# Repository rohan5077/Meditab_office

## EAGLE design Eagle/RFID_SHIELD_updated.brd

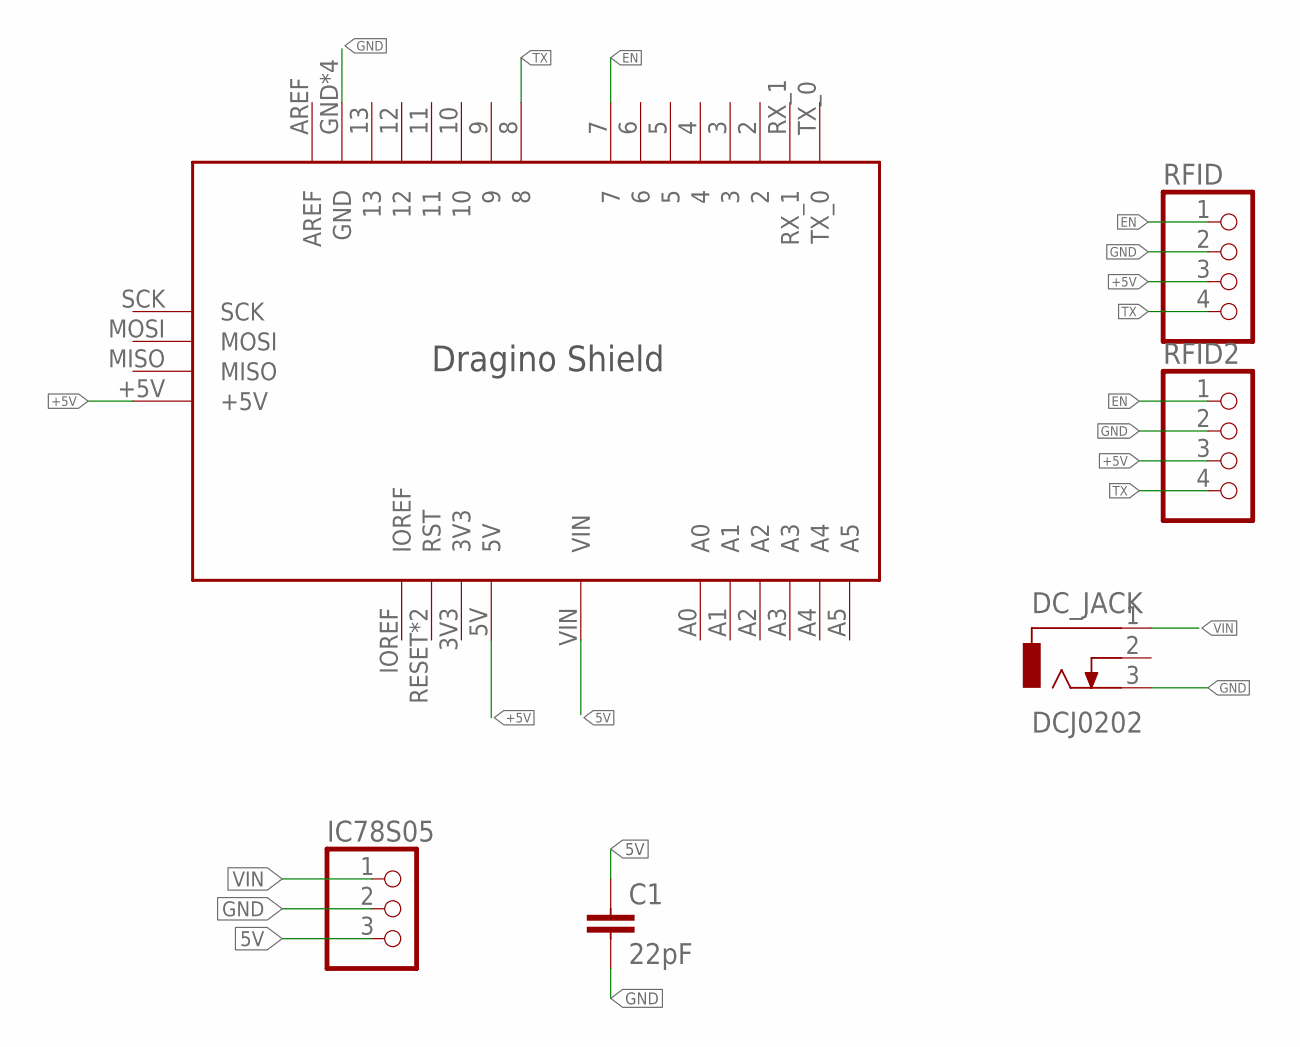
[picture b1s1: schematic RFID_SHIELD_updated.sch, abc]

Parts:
C1: 22pF; C2.5-3
DC_JACK: DCJ0202
IC78S05: PINHD-1X3; 1X03
RFID, RFID2: PINHD-1X4; 1X04
U$1: DRAGINO_SHIELD

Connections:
5V: C1.1, IC78S05.3, U$1.VIN
+5V: RFID.3, RFID2.3, U$1.5V, U$1.+5V
EN: RFID.1, RFID2.1, U$1.7
GND: C1.2, DC_JACK.3, IC78S05.2, RFID.2, RFID2.2, U$1.GND, U$1.GND@1 (GND), U$1.GND@2 (GND), U$1.GND@3 (GND)
TX: RFID.4, RFID2.4, U$1.8
VIN: DC_JACK.1, IC78S05.1

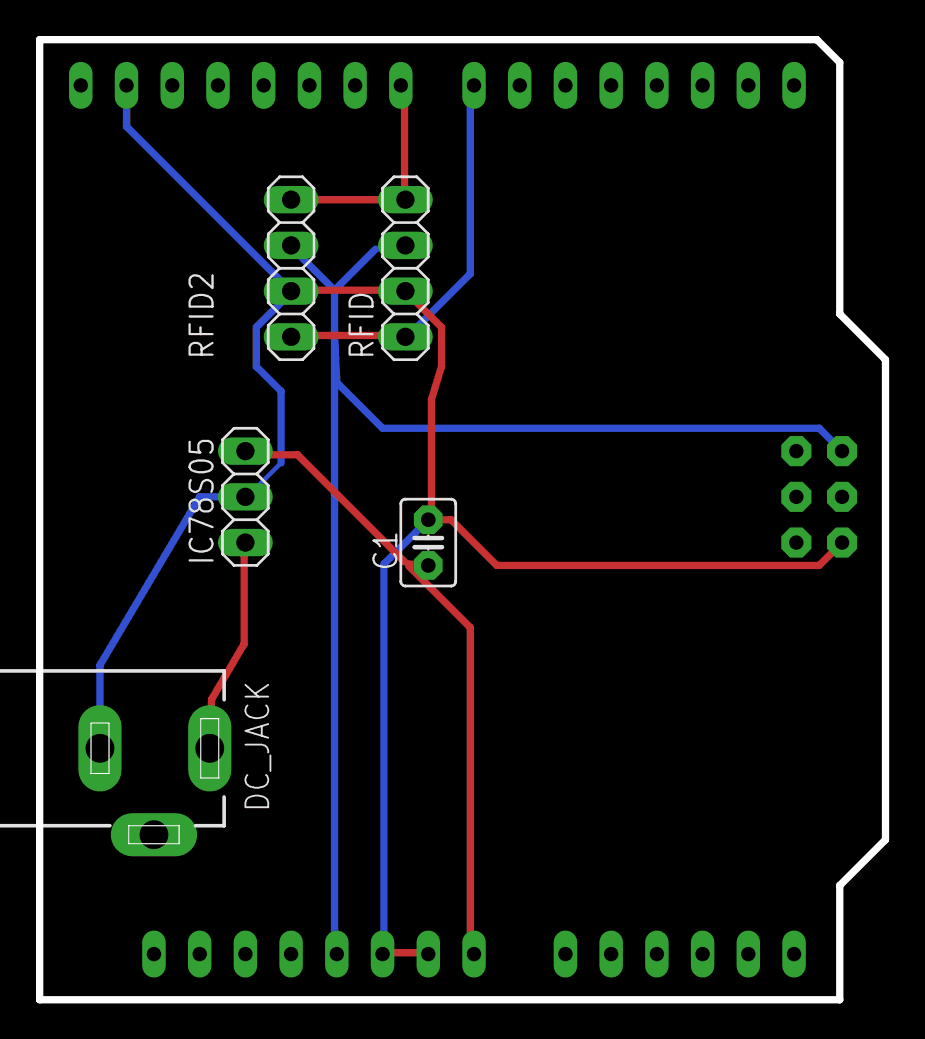
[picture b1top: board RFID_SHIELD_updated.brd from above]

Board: 2 copper layers, 47.0 x 53.3 mm, 6 parts (0 on the bottom side), 6 nets.

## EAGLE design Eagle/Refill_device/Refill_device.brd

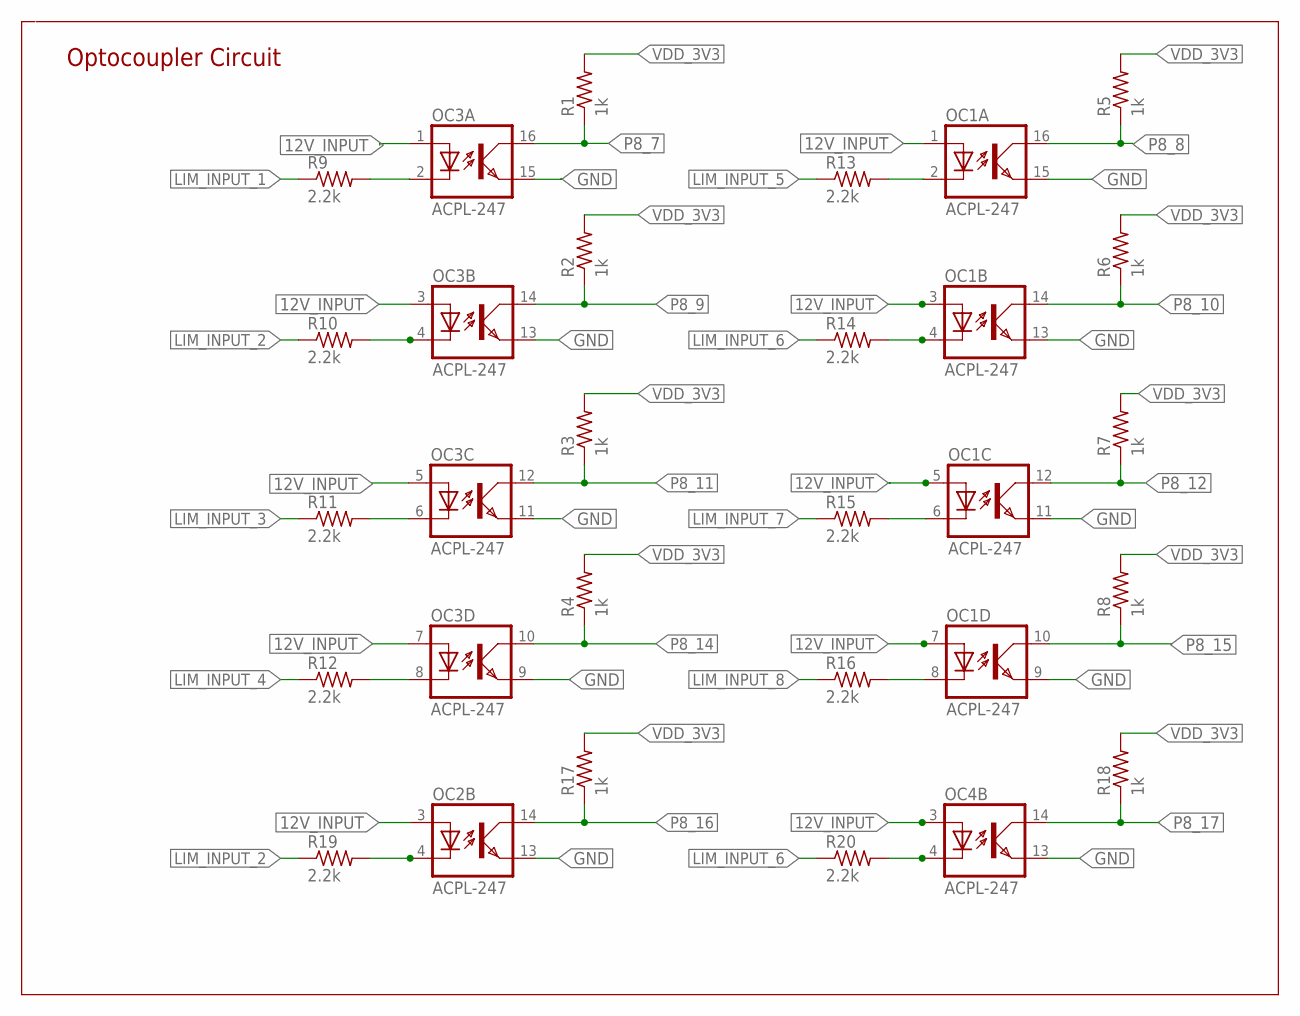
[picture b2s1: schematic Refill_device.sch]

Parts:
OC1, OC2, OC3, OC4: ACPL-247; SOP16
R1, R2, R3, R4, R5, R6, R7, R8, R17, R18: 1k; R0603
R9, R10, R11, R12, R13, R14, R15, R16, R19, R20: 2.2k; R0603

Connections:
12V_INPUT: OC1.1 (A), OC1.3 (A), OC1.5 (A), OC1.7 (A), OC2.3 (A), OC3.1 (A), OC3.3 (A), OC3.5 (A), OC3.7 (A), OC4.3 (A)
GND: OC1.9 (EMIT), OC1.11 (EMIT), OC1.13 (EMIT), OC1.15 (EMIT), OC2.13 (EMIT), OC3.9 (EMIT), OC3.11 (EMIT), OC3.13 (EMIT), OC3.15 (EMIT), OC4.13 (EMIT)
LIM_INPUT_1: R9.1
LIM_INPUT_2: R10.1, R19.1
LIM_INPUT_3: R11.1
LIM_INPUT_4: R12.1
LIM_INPUT_5: R13.1
LIM_INPUT_6: R14.1, R20.1
LIM_INPUT_7: R15.1
LIM_INPUT_8: R16.1
unnamed: OC4.4 (C), R20.2
unnamed: OC2.4 (C), R19.2
unnamed: OC1.2 (C), R13.2
unnamed: OC1.4 (C), R14.2
unnamed: OC1.6 (C), R15.2
unnamed: OC1.8 (C), R16.2
unnamed: OC3.6 (C), R11.2
unnamed: OC3.8 (C), R12.2
unnamed: OC3.2 (C), R9.2
unnamed: OC3.4 (C), R10.2
P8_7: OC3.16 (COL), R1.1
P8_8: OC1.16 (COL), R5.1
P8_9: OC3.14 (COL), R2.1
P8_10: OC1.14 (COL), R6.1
P8_11: OC3.12 (COL), R3.1
P8_12: OC1.12 (COL), R7.1
P8_14: OC3.10 (COL), R4.1
P8_15: OC1.10 (COL), R8.1
P8_16: OC2.14 (COL), R17.1
P8_17: OC4.14 (COL), R18.1
VDD_3V3: R1.2, R2.2, R3.2, R4.2, R5.2, R6.2, R7.2, R8.2, R17.2, R18.2

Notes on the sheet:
Optocoupler Circuit

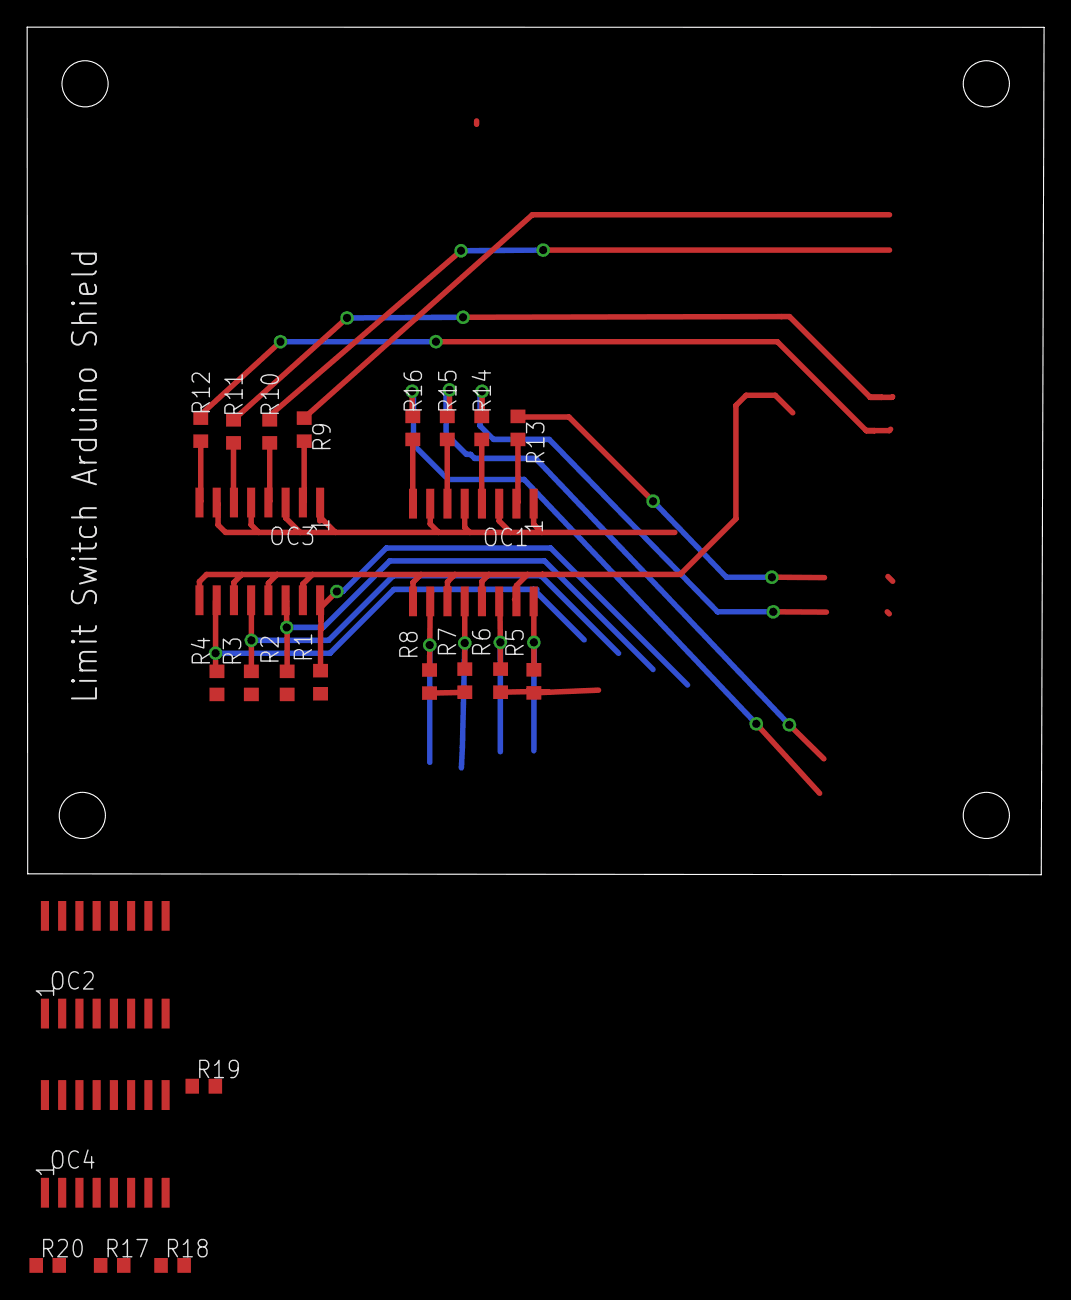
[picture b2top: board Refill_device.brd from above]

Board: 2 copper layers, 74.9 x 62.4 mm, 24 parts (0 on the bottom side), 25 nets.

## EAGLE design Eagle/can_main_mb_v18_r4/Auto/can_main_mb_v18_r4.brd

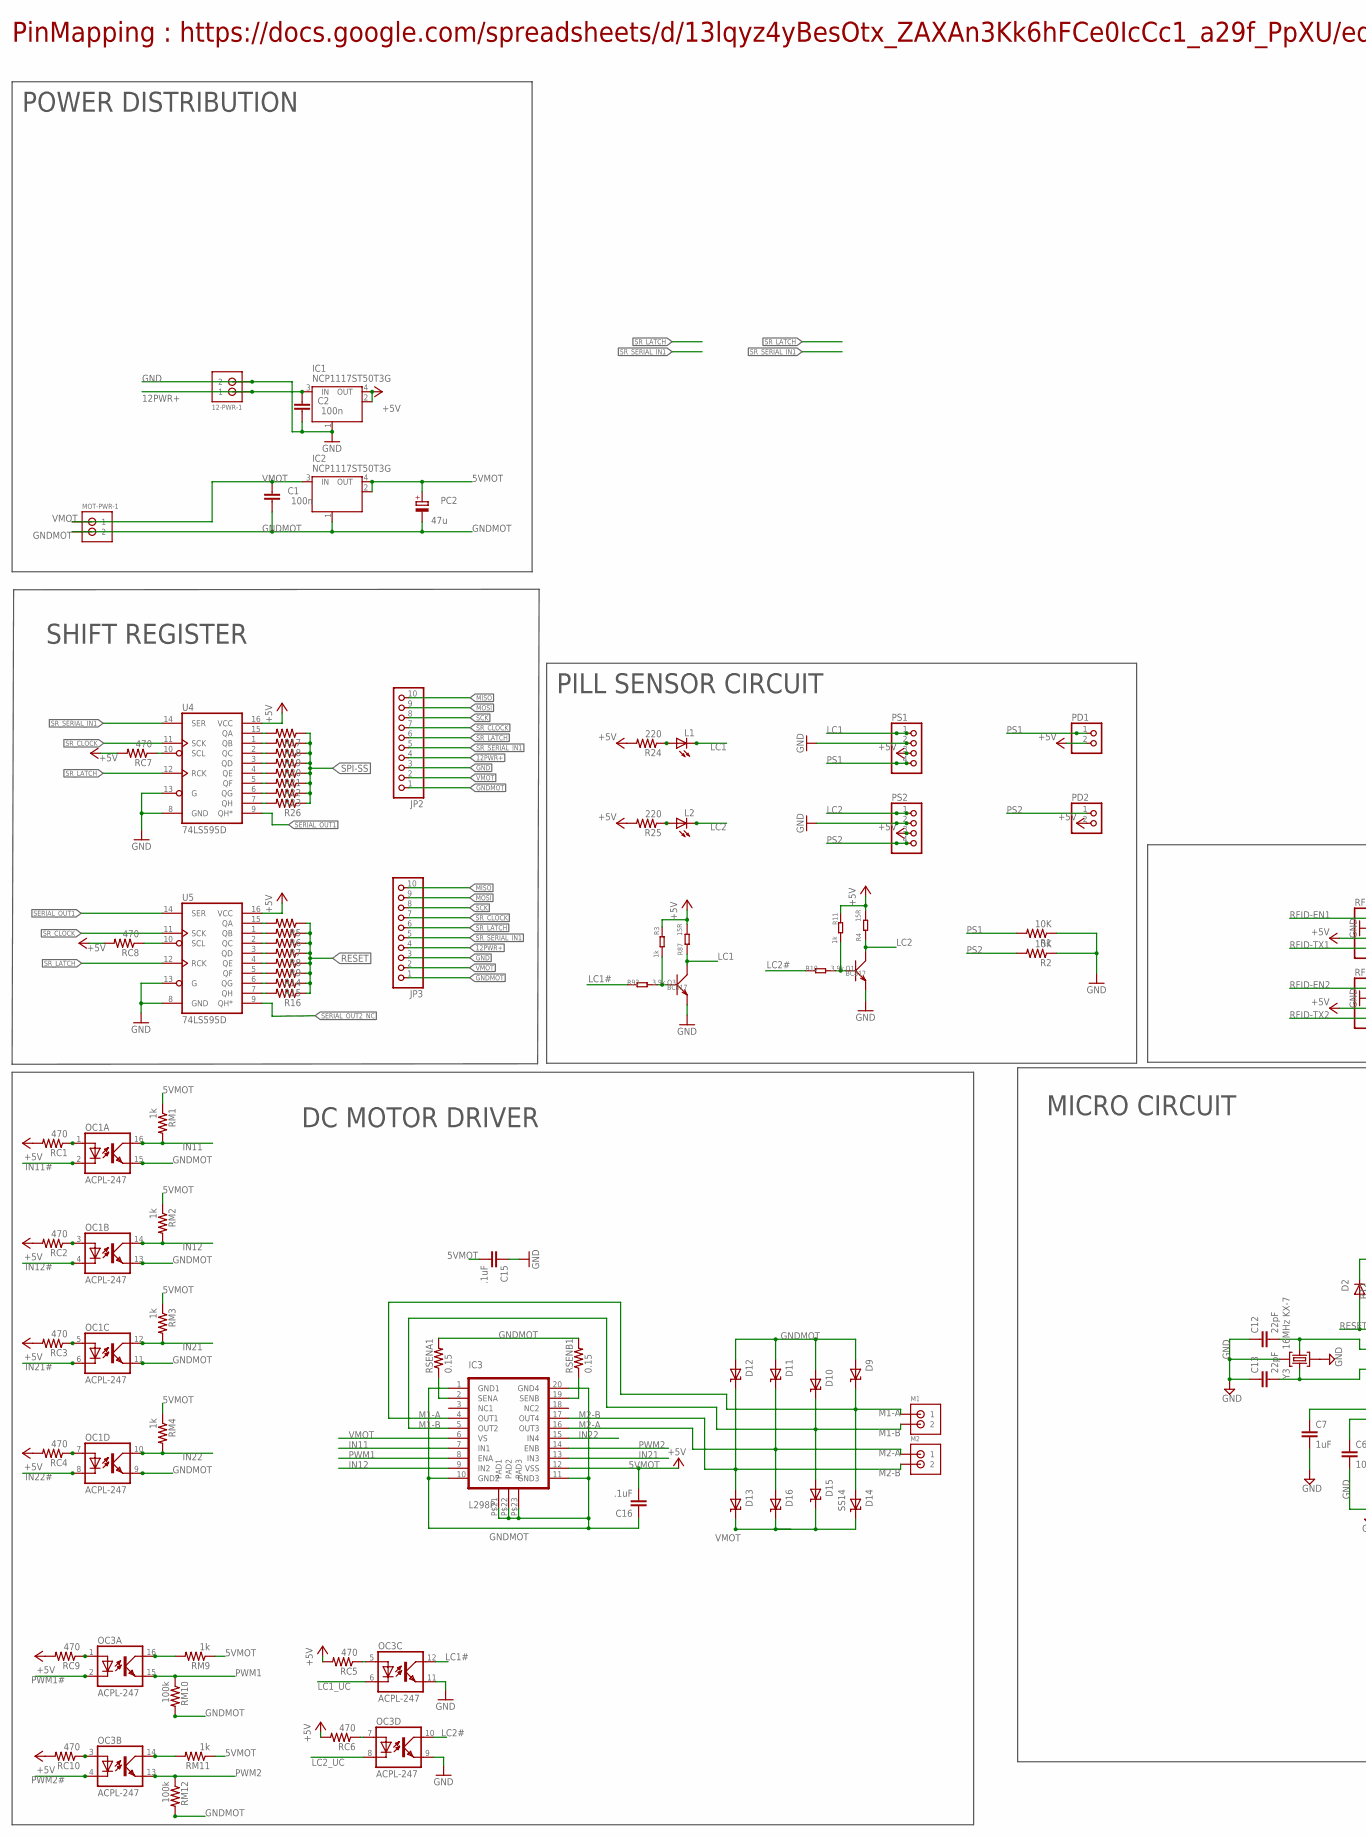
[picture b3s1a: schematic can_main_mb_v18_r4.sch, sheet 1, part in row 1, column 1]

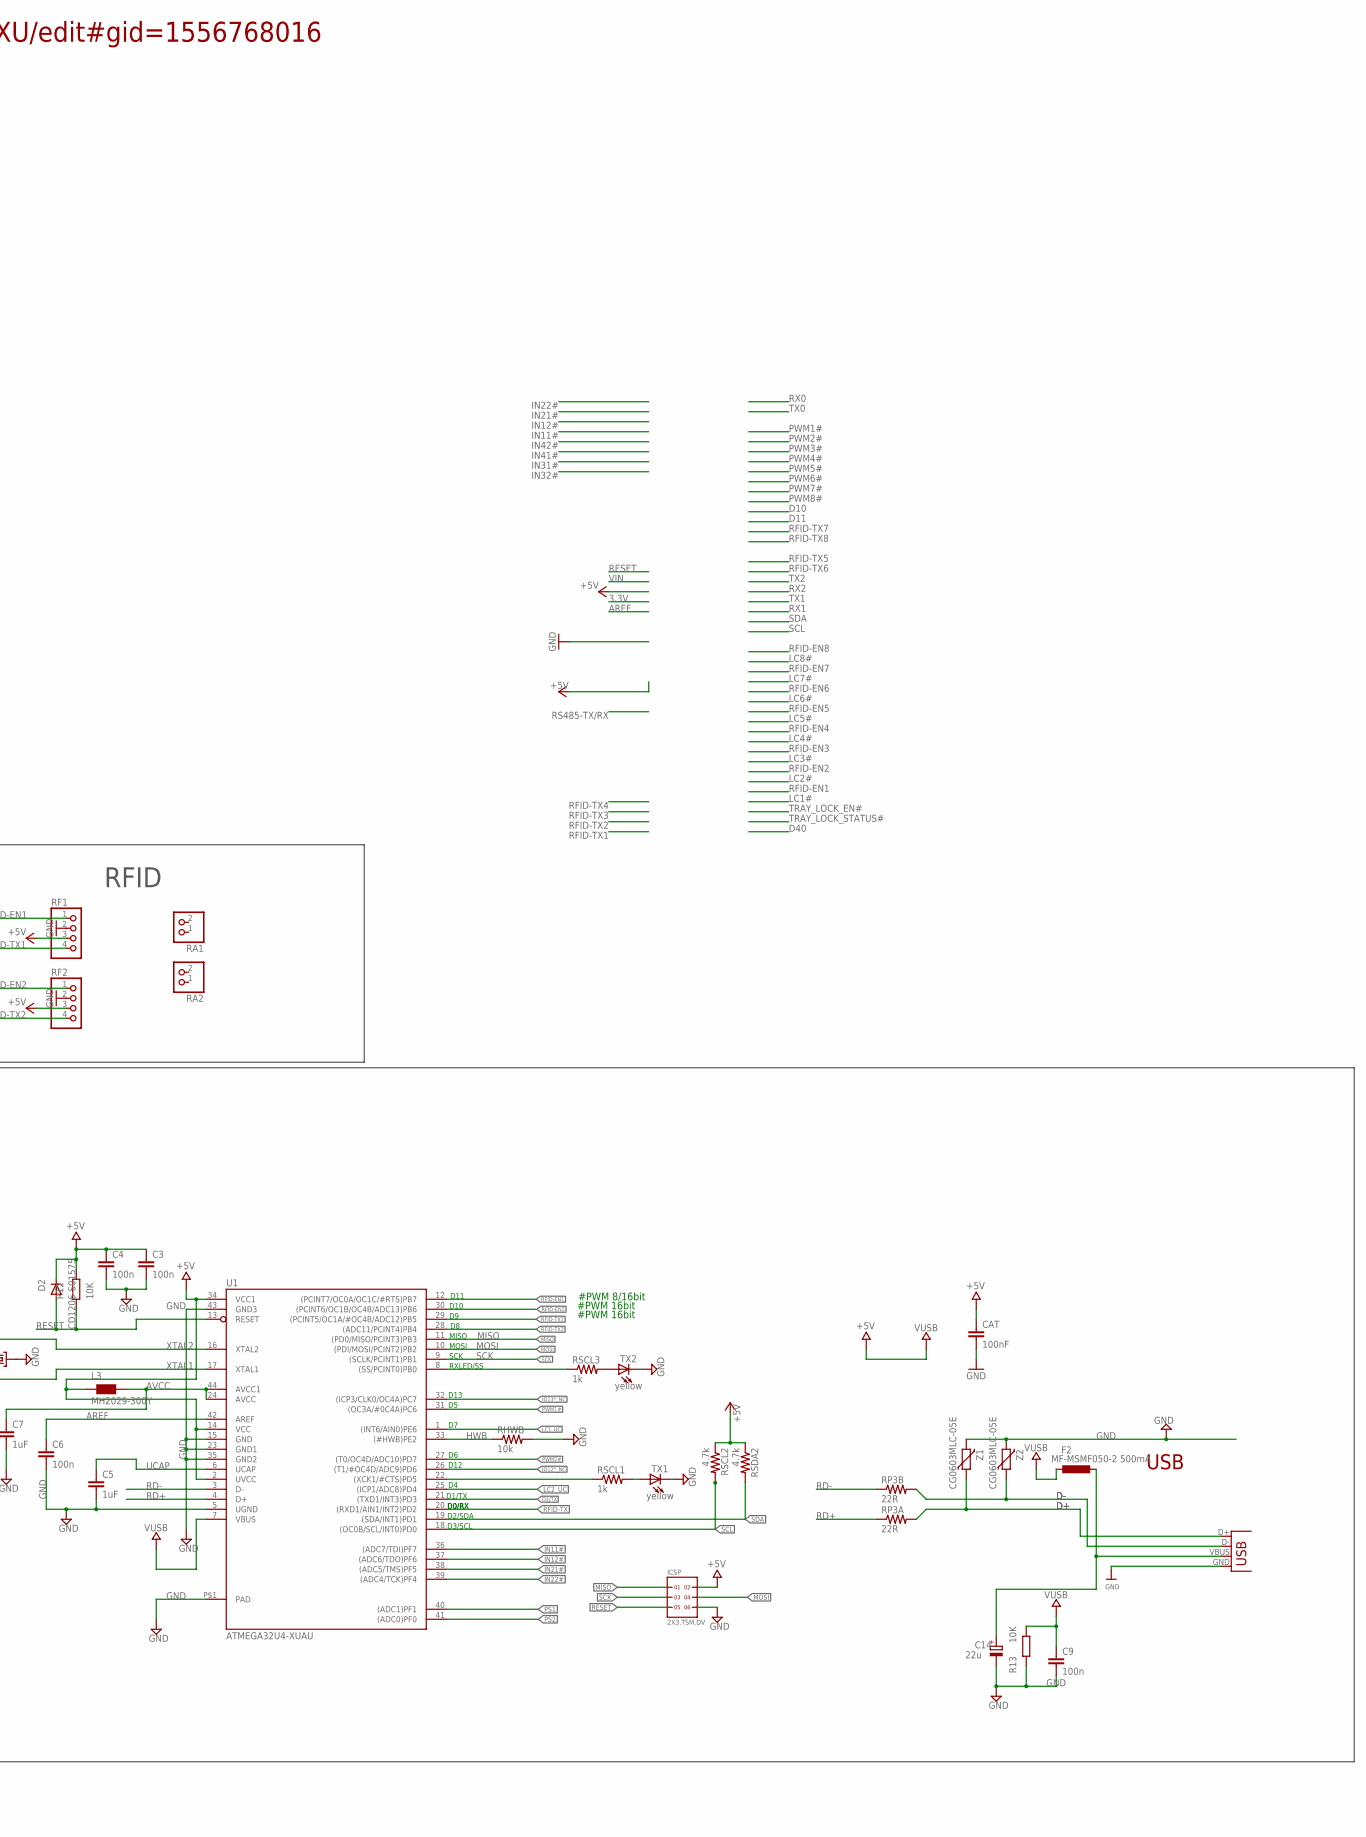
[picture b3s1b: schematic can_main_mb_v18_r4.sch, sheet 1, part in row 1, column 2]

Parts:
12-PWR-1: JST-PH_2-PIN_HEADER; JST_B2B-PH_HEADER
C1, C2: 100n; C0603
C3, C4, C6, C9: 100n; C0603K
C5, C7: 1uF; C0603K
C12, C13: 22pF; C0603K
C14: 22u; SMC_C
C15, C16: .1uF; 0402-CAP
CAT: 100nF; 0603
D2: CD1206-S01575; MINIMELF
D9, D10, D11, D12, D13, D14, D15, D16: SS14; SMA
F2: MF-MSMF050-2 500mA; L1812
IC1, IC2: NCP1117ST50T3G; SOT223
IC3: L298P; POWER-SO20
ICSP: 2X3.TSM.DV; TSM-103-XX-XXX-DV-A
JP1: USB; USB-B-PTH-VERTICAL
JP2, JP3: PINHD-1X10; 1X10
L1, L2: LED5MM
L3: MH2029-300Y; 0805
M1, M2: JST-PH_2-PIN_HEADER; JST_B2B-PH_HEADER
MOT-PWR-1: JST-PH_2-PIN_HEADER; JST_B2B-PH_HEADER
OC1, OC3: ACPL-247; SOP16
PC2: 47u; PANASONIC_D
PD1, PD2: PINHD-1X2; 1X02
PS1, PS2: PINHD-1X4; 1X04
Q1, Q3: BC817; SOT23
R1, R2: 10K; R0603
R3, R11: 1k; R0603
R4, R87: 15R; R0603
R5, R6, R7, R8, R9, R14, R15, R16, R17, R18, R19, R20, R21, R22, R23, R26: R-US_R0603; R0603
R10, R93: 3.9k; R0603
R12, R13: 10K; R0603-ROUND
R24, R25: 220; R0603
RA1, RA2: PINHD-1X2; 1X02
RC1, RC2, RC3, RC4, RC5, RC6, RC7, RC8, RC9, RC10: 470; R0603
RF1, RF2: PINHD-1X4; 1X04
RHWB: 10k; R0603
RM1, RM2, RM3, RM4, RM9, RM11: 1k; R0603
RM10, RM12: 100k; R0603
RP3A, RP3B: 22R; R0603
RSCL1, RSCL3: 1k; R0603
RSCL2: 4.7k; R0603
RSDA2: 4.7k; R0603
RSENA1: 0.15; R0603
RSENB1: 0.15; R0603
TX1, TX2: yellow; CHIPLED_0603
U1: ATMEGA32U4-XUAU; TQFP44-PAD
U4, U5: 74LS595D; SO16
Y3: 16MHz KX-7; CRYSTAL-3.2-2.5
Z1, Z2: CG0603MLC-05E; CT/CN0603

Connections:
5VMOT: C15.2, C16.2, IC2.2 (OUT), IC2.4 (OUT), IC3.P$12 (VSS), PC2.+, RM1.1, RM2.1, RM3.1, RM4.1, RM9.1, RM11.1
12PWR+: 12-PWR-1.P1 (1), C2.2, IC1.3 (IN), JP2.4, JP3.4
+5V: C3.1, C4.1, C9.1, CAT.1, D2.C, F2.2, IC1.2 (OUT), IC1.4 (OUT), ICSP.2, L3.1, PD1.2, PD2.2, PS1.3, PS2.3, R3.1, R4.2, R11.1, R12.1, R13.2, R24.2, R25.2, R87.2, RC1.2, RC2.2, RC3.2, RC4.2, RC5.2, RC6.2, RC7.2, RC8.2, RC9.2, RC10.2, RF1.3, RF2.3, RSCL2.1, RSDA2.1, U1.2 (UVCC), U1.7 (VBUS), U1.14 (VCC), U1.34 (VCC1), U4.16 (VCC), U5.16 (VCC)
AREF: C6.1, U1.42 (AREF)
AVCC: C7.1, L3.2, U1.24 (AVCC), U1.44 (AVCC1)
D1/TX: U1.21 ((TXD1/INT3)PD3)
D+: JP1.D+, RP3A.2, Z1.1
D-: JP1.D-, RP3B.2, Z2.1
GND: 12-PWR-1.P2 (2), C2.1, C3.2, C4.2, C5.2, C6.2, C7.2, C9.2, C12.1, C13.1, C14.-, CAT.2, IC1.1 (GND/ADJ), ICSP.6, JP1.GND, JP2.3, JP3.3, OC3.9 (EMIT), OC3.11 (EMIT), PS1.2, PS2.2, Q1.2 (E), Q3.2 (E), R1.1, R2.1, R13.1, RF1.2, RF2.2, RHWB.2, TX1.C, TX2.C, U1.5 (UGND), U1.15 (GND), U1.23 (GND1), U1.35 (GND2), U1.43 (GND3), U1.P$1 (PAD), U4.8 (GND), U4.13 (G), U5.8 (GND), U5.13 (G), Y3.2 (GND), Y3.4 (GND), Z1.2, Z2.2
GNDMOT: C1.1, C15.1, C16.1, D9.P$2 (A), D10.P$2 (A), D11.P$2 (A), D12.P$2 (A), IC2.1 (GND/ADJ), IC3.P$1 (GND1), IC3.P$10 (GND2), IC3.P$11 (GND3), IC3.P$20 (GND4), IC3.P$21 (PAD1), IC3.P$22 (PAD2), IC3.P$23 (PAD3), JP2.1, JP3.1, MOT-PWR-1.P2 (2), OC1.9 (EMIT), OC1.11 (EMIT), OC1.13 (EMIT), OC1.15 (EMIT), PC2.-, RM10.2, RM12.2, RSENA1.2, RSENB1.2
HWB: RHWB.1, U1.33 ((#HWB)PE2)
IN11: IC3.P$7 (IN1), OC1.16 (COL), RM1.2
IN11#: OC1.2 (C), U1.36 ((ADC7/TDI)PF7)
IN12: IC3.P$9 (IN2), OC1.14 (COL), RM2.2
IN12#: OC1.4 (C), U1.37 ((ADC6/TDO)PF6)
IN21: IC3.P$13 (IN3), OC1.12 (COL), RM3.2
IN21#: OC1.6 (C), U1.38 ((ADC5/TMS)PF5)
IN22: IC3.P$15 (IN4), OC1.10 (COL), RM4.2
IN22#: OC1.8 (C), U1.39 ((ADC4/TCK)PF4)
IO12*_NC: U1.26 ((T1/#OC4D/ADC9)PD6)
IO13*_NC: U1.32 ((ICP3/CLK0/OC4A)PC7)
LC1: L1.K (C), PS1.1, Q3.3 (C), R87.1
LC1#: OC3.12 (COL), R93.1
LC1_UC: OC3.6 (C), U1.1 ((INT6/AIN0)PE6)
LC2: L2.K (C), PS2.1, Q1.3 (C), R4.1
LC2#: OC3.10 (COL), R10.1
LC2_UC: OC3.8 (C), U1.25 ((ICP1/ADC8)PD4)
M1-A: D9.P$1 (K), D14.P$2 (A), IC3.P$4 (OUT1), M1.P1 (1)
M1-B: D10.P$1 (K), D15.P$2 (A), IC3.P$5 (OUT2), M1.P2 (2)
M2-A: D11.P$1 (K), D16.P$2 (A), IC3.P$16 (OUT3), M2.P1 (1)
M2-B: D12.P$1 (K), D13.P$2 (A), IC3.P$17 (OUT4), M2.P2 (2)
MISO: ICSP.1, JP2.10, JP3.10, U1.11 ((PD0/MISO/PCINT3)PB3)
MOSI: ICSP.4, JP2.9, JP3.9, U1.10 ((PDI/MOSI/PCINT2)PB2)
unnamed: OC1.3 (A), RC2.1
unnamed: OC1.5 (A), RC3.1
unnamed: OC3.5 (A), RC5.1
unnamed: OC1.7 (A), RC4.1
unnamed: RC8.1, U5.10 (SCL)
unnamed: OC3.7 (A), RC6.1
unnamed: Q1.1 (B), R10.2, R11.2
unnamed: RC7.1, U4.10 (SCL)
unnamed: OC3.1 (A), RC9.1
unnamed: OC3.3 (A), RC10.1
unnamed: RSCL1.1, U1.22 ((XCK1/#CTS)PD5)
unnamed: R5.2, U5.15 (QA)
unnamed: L1.A, R24.1
unnamed: R6.2, U5.1 (QB)
unnamed: R7.2, U5.2 (QC)
unnamed: R8.2, U5.3 (QD)
unnamed: R16.2, U5.7 (QH)
unnamed: RSCL1.2, TX1.A
unnamed: RSCL3.2, TX2.A
unnamed: R15.2, U5.6 (QG)
unnamed: R9.2, U5.4 (QE)
unnamed: R17.2, U4.15 (QA)
unnamed: R18.2, U4.1 (QB)
unnamed: R19.2, U4.2 (QC)
unnamed: R20.2, U4.3 (QD)
unnamed: R26.2, U4.7 (QH)
unnamed: R23.2, U4.6 (QG)
unnamed: R21.2, U4.4 (QE)
unnamed: R14.2, U5.5 (QF)
unnamed: L2.A, R25.1
unnamed: OC3.16 (COL), RM9.2
unnamed: OC3.14 (COL), RM11.2
unnamed: OC1.1 (A), RC1.1
unnamed: Q3.1 (B), R3.2, R93.2
PS1: PD1.1, PS1.4, R1.2, U1.40 ((ADC1)PF1)
PS2: PD2.1, PS2.4, R2.2, U1.41 ((ADC0)PF0)
PWM1: IC3.P$8 (ENA), OC3.15 (EMIT), RM10.1
PWM1#: OC3.2 (C), U1.31 ((OC3A/#0C4A)PC6)
PWM2: IC3.P$14 (ENB), OC3.13 (EMIT), RM12.1
PWM2#: OC3.4 (C), U1.27 ((T0/OC4D/ADC10)PD7)
RD+: RP3A.1, U1.4 (D+)
RD-: RP3B.1, U1.3 (D-)
RESET: D2.A, ICSP.5, R5.1, R6.1, R7.1, R8.1, R9.1, R12.2, R14.1, R15.1, R16.1, U1.13 (RESET)
RESET1: R22.2, U4.5 (QF)
RFID-EN1: RF1.1, U1.12 ((PCINT7/OC0A/OC1C/#RTS)PB7)
RFID-EN2: RF2.1, U1.30 ((PCINT6/OC1B/OC4B/ADC13)PB6)
RFID-TX: U1.20 ((RXD1/AIN1/INT2)PD2)
RFID-TX1: RF1.4, U1.29 ((PCINT5/OC1A/#OC4B/ADC12)PB5)
RFID-TX2: RF2.4, U1.28 ((ADC11/PCINT4)PB4)
SCK: ICSP.3, JP2.8, JP3.8, U1.9 ((SCLK/PCINT1)PB1)
SCL: RSCL2.2, U1.18 ((OC0B/SCL/INT0)PD0)
SDA: RSDA2.2, U1.19 ((SDA/INT1)PD1)
SERIAL_OUT1: U4.9 (QH*), U5.14 (SER)
SERIAL_OUT2_NC: U5.9 (QH*)
SNSA: IC3.P$2 (SENA), RSENA1.1
SNSB: IC3.P$19 (SENB), RSENB1.1
SPI-SS: R17.1, R18.1, R19.1, R20.1, R21.1, R22.1, R23.1, R26.1, RSCL3.1, U1.8 ((SS/PCINT0)PB0)
SR_CLOCK: JP2.7, JP3.7, U4.11 (SCK), U5.11 (SCK)
SR_LATCH: JP2.6, JP3.6, U4.12 (RCK), U5.12 (RCK)
SR_SERIAL_IN1: JP2.5, JP3.5, U4.14 (SER)
UCAP: C5.1, U1.6 (UCAP)
VMOT: C1.2, D13.P$1 (K), D14.P$1 (K), D15.P$1 (K), D16.P$1 (K), IC2.3 (IN), IC3.P$6 (VS), JP2.2, JP3.2, MOT-PWR-1.P1 (1)
VUSBD: C14.+, F2.1, JP1.VBUS
XTAL1: C13.2, U1.17 (XTAL1), Y3.3 (C2)
XTAL2: C12.2, U1.16 (XTAL2), Y3.1 (C1)

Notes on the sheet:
USB
#PWM 8/16bit
#PWM 16bit
D0/RX
D1/TX
D2/SDA
D3/SCL
D12
D13
RXLED/SS
SCK
MOSI
MISO
D10
D11
PinMapping : https://docs.google.com/spreadsheets/d/13lqyz4yBesOtx_ZAXAn3Kk6hFCe0IcCc1_a29f_PpXU/edit#gid=1556768016
PILL SENSOR CIRCUIT
POWER DISTRIBUTION
DC MOTOR DRIVER
MICRO CIRCUIT
SHIFT REGISTER
RFID

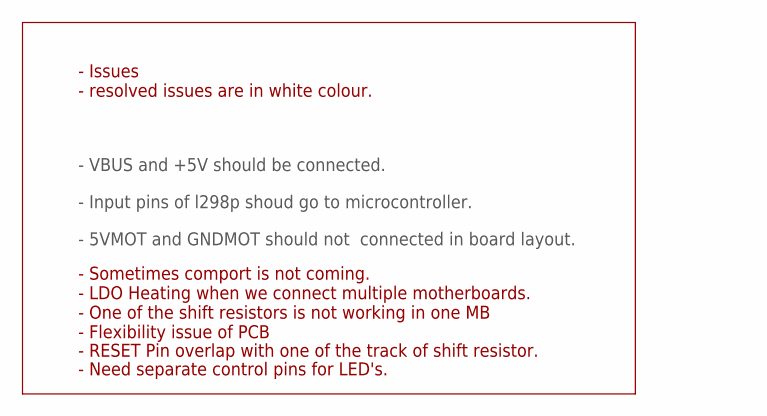
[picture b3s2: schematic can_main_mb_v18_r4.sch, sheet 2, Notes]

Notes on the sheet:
- VBUS and +5V should be connected.
- Input pins of l298p shoud go to microcontroller.
- 5VMOT and GNDMOT should not connected in board layout.
- Issues - resolved issues are in white colour.
- Sometimes comport is not coming. - LDO Heating when we connect multiple motherboards. - One of the shift resistors is not working in one MB - Flexibility issue of PCB
- RESET Pin overlap with one of the track of shift resistor.
- Need separate control pins for LED's.

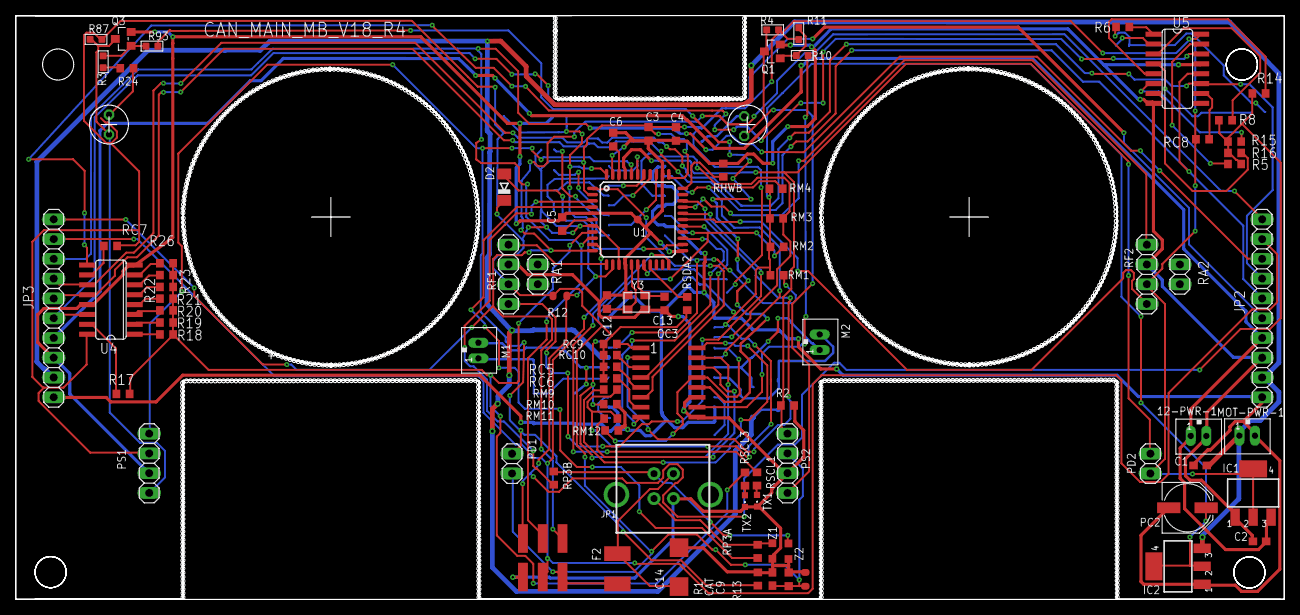
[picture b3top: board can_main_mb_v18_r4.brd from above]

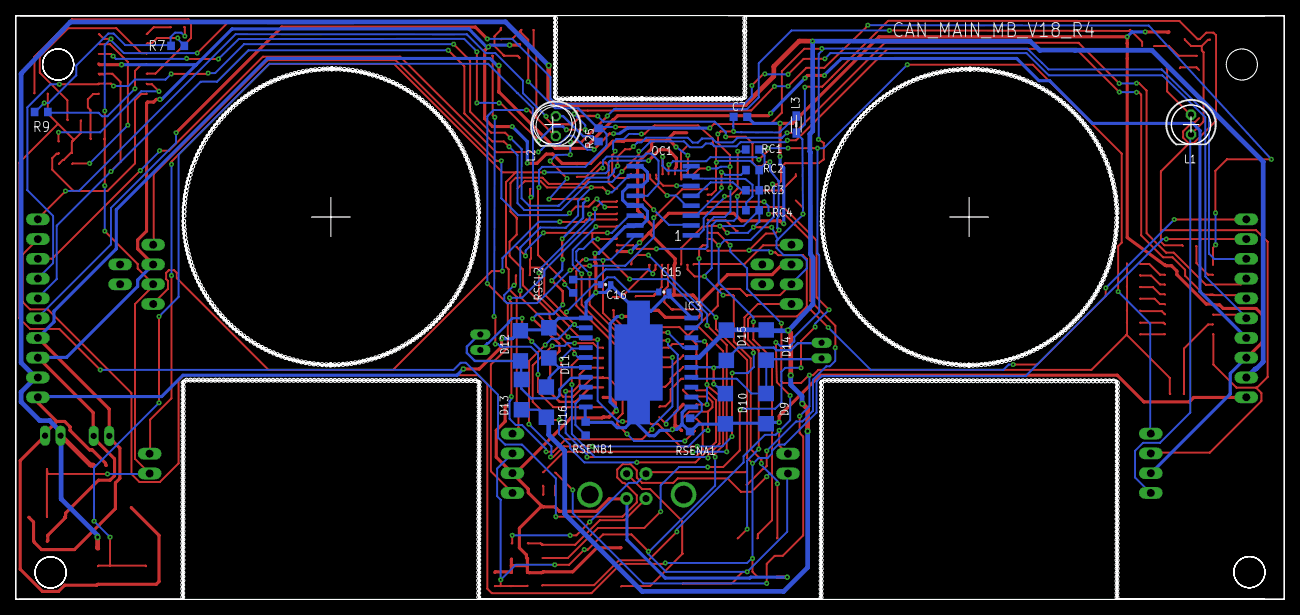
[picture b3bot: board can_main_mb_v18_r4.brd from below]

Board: 4 copper layers, 163.0 x 75.0 mm, 114 parts (26 on the bottom side), 93 nets.

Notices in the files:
parts and their libraries:
SparkFun-LED: Licensing: CC v3.0 Share-Alike You are welcome to use this library for commercial purposes.
SparkFun-Connectors: Licensing: Creative Commons ShareAlike 4.0 International - https://creativecommons.org/licenses/by-sa/4.0
